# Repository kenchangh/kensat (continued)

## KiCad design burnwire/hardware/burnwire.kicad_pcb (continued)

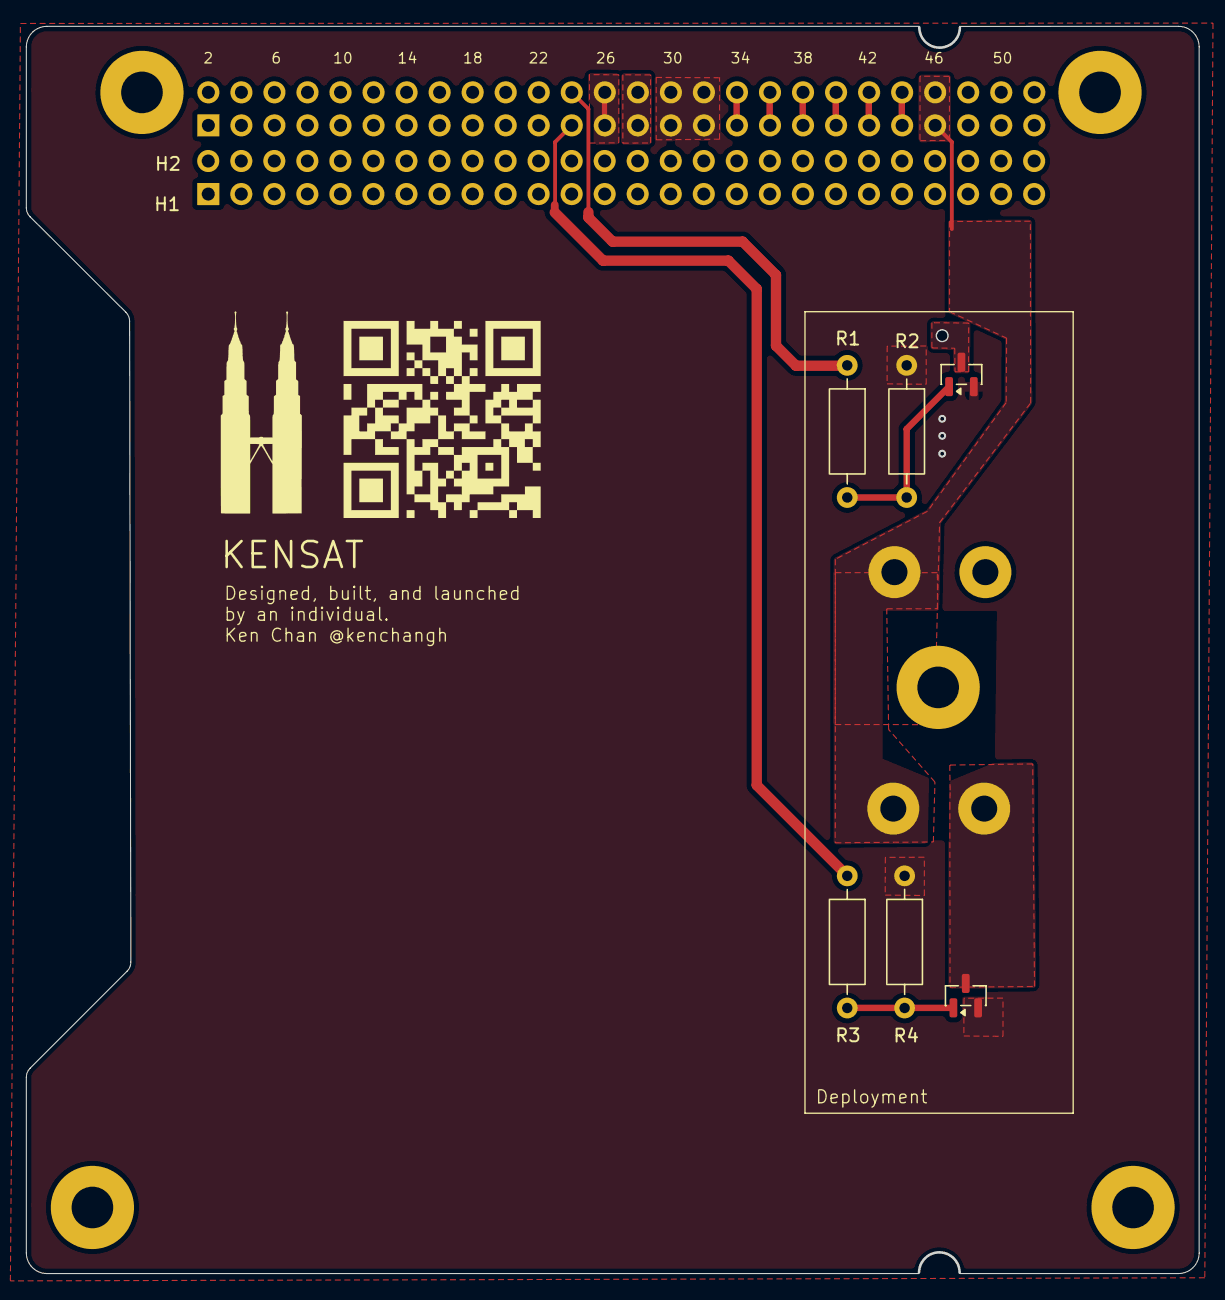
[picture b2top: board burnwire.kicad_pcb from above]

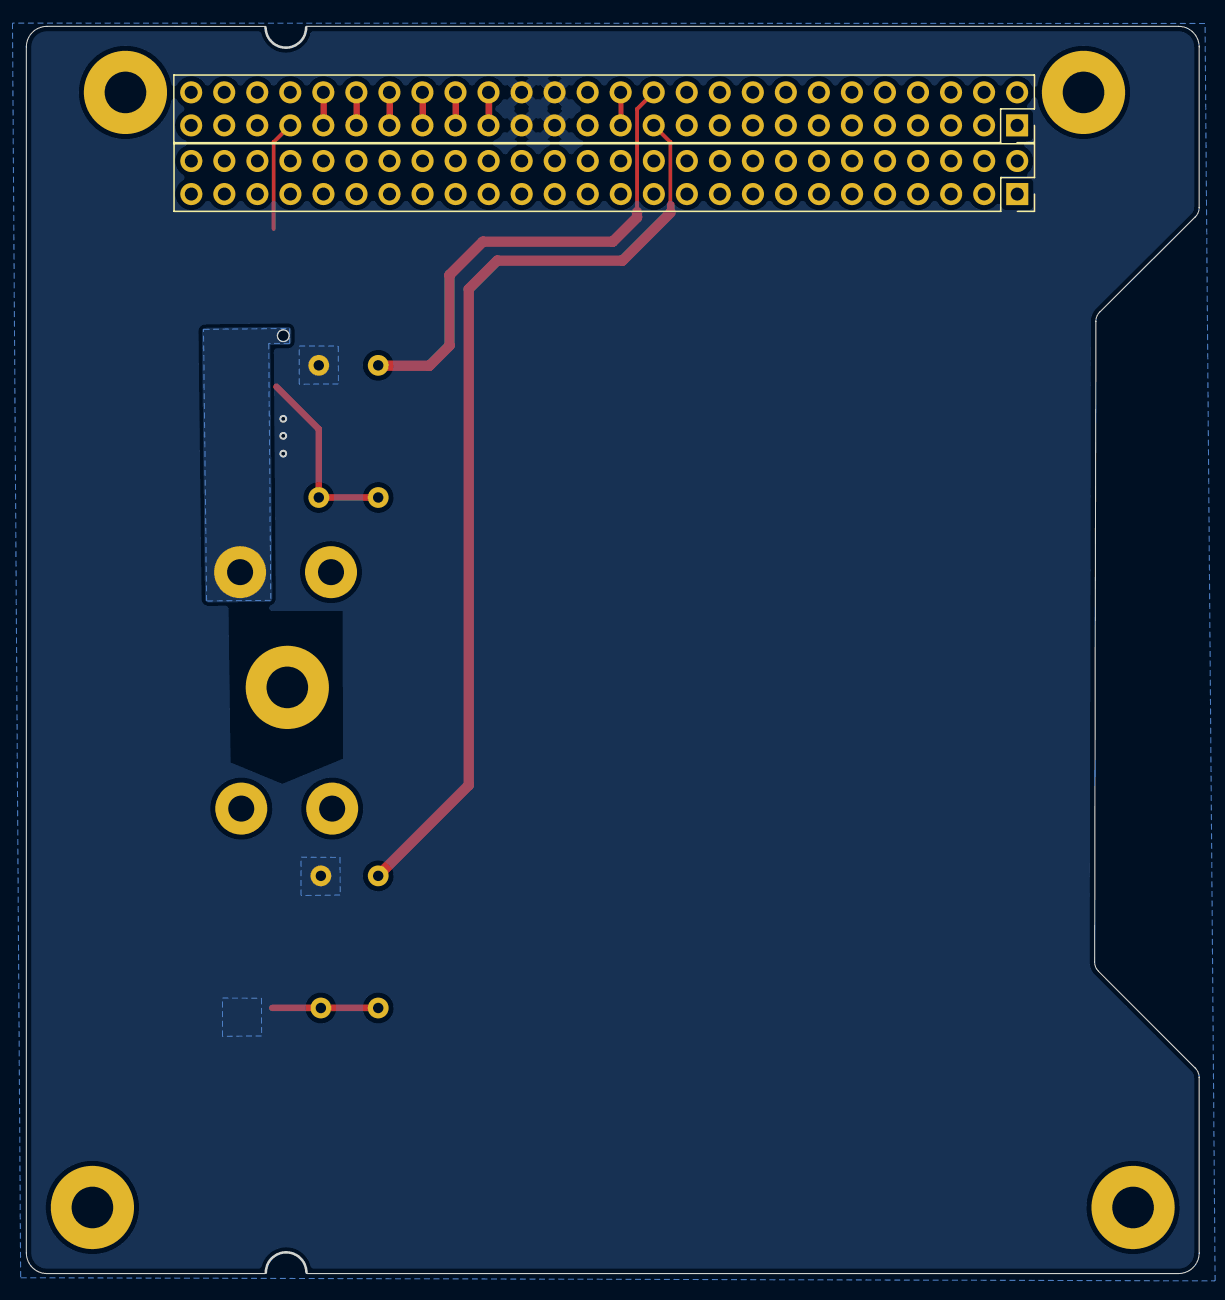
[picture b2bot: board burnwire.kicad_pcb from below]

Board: 2 copper layers, 90.2 x 95.9 mm, 8 parts (2 on the bottom side), 14 nets.

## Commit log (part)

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2026-06-17 Consolidate KENSAT CubeSat into a single repository
    Bring the full 2U CubeSat project together from three formerly separate
    working directories (radio, burnwire, OBC/Pumpkin) into one structured,
    portfolio-ready repo:
    - firmware/obc — PIC24 flight software (app/ mission logic + bsp/ drivers)
    - radio — Si4463 UHF board: ESP32 firmware, KiCad design, RF matching
    - eps — electrical power system board (KiCad)
2026-06-23 Reframe docs around edge-AI compute in orbit
    Lead the documentation with KENSAT's primary mission — running LLM inference
    on a power-gated Jetson Orin Nano payload in orbit and downlinking results —
    and present the other subsystems as serving that goal. De-emphasize the
    single-engineer / first-individual framing in the top README, system
    architecture overview, and radio README.
2026-06-23 Add burn-wire board as Slot 4 to the physical stack
    The antenna-release burn-wire board (resistive heating) is the top board in
    the 2U stack. Update the stack diagram (README), the physical-stack table
    (system architecture), and the burn-wire / EPS slot references accordingly.
2026-06-23 Remove generated BOM and placement CSVs from hardware
    Drop the JLCPCB BOM and component-placement (pos/CPL) CSVs for the radio and
    burn-wire boards — these are generated fabrication outputs, not design sources.
    Ignore */hardware/*.csv going forward and update the radio/burn-wire READMEs.
2026-06-23 Remove SDR demodulator bring-up scratch scripts
    Drop the 16 one-off diagnose_*/find_carrier scripts written while bringing up
    the demodulator. They were heavily overlapping debug artifacts; the working
    result lives in beacon_decoder.py and pluto_rx_ax25.py. Trim the ground-station
    README accordingly.
2026-06-23 Add assembled CubeSat photo to README
    Embed a bench photo of the integrated 2U flatsat under the intro so the
    README leads with the physical hardware.
2026-06-23 Convert README photo from HDR/PQ to sRGB
    The original was a Display-P3 PQ HDR JPEG with a gain map, which renders
    washed-out grey in non-HDR browsers and viewers. Tone-map to standard sRGB
    (SDR) via ColorSync and downscale to 1600px so it displays correctly and
    consistently everywhere, including GitHub.
